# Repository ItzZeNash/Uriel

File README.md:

Fully assembled in fusion 
For assembly solder on the kalih hotswap sockets, the jst connector which is through hold along with the nice!nano clone which is mounted on the backside of the board flipped. The diodes should also be soldered on the backside with the black line on the side of the sqaure hole.Also connect the battery with the jst connector.  After that put on the orings on the protrusions on the pcb then put it into the case(the case should already have 5 layers put together(the solid base the hollow rings x 3, and the gasket holder, after that lay it onto the gasket holder which will support the pcb, then add the other gasket holder to make sure it holds, then add the top 2 whihc inlude a cutout for the usb, then add screws to fasten the case. After that add the m2 standoffs on the pcb where the controller and the silkscreen is then add it onto the holds then screw onto the small acrylic cover and you are finished.

Idk how to do keycaps and nice nano itll be also itll be wayy to complicated for me ._.

# Uriel
A 40% keyboard 
PCB - 

Schem-

Bom

# Bill of Materials (BOM) — Custom 40% Keybiard

| # | Component | Qty | Description / Specs | Part / Model | Price (USD) | Source / Link | Notes |
|---|-----------|-----|---------------------|--------------|-------------|----------------|-------|
| 1 | Wireless Controller | 2 | NRF52840 dev board, Nice!Nano v2 compatible, BLE + charging, Pro Micro footprint | Nice!Nano alternative | **$4.34 each ($8.68)** | https://www.ebay.com/itm/405014063318 | Use as nice_nano_v2 in ZMK. Deep sleep ~1mA. |
| 2 | Keyboard Switches | 90 | Akko Rosewood Linear, 5-pin MX, 40gf, factory lubed | Akko Rosewood | **$29.46 total** | https://www.aliexpress.com/item/1005007227966289.html | 47 used, extras for future builds. |
| 3 | Switching Diodes | 50 | 1N4148 | 1N4148 pack | **$3.00** | https://www.mouser.com/ProductDetail/onsemi/1N4148TR?qs=i4Fj9T%2FoRm%252BOzV8sfXrhvQ%3D%3D | 1 per key + spares. |
| 4 | Reset Tactile Switch | 2 | Right-angle, grounding, 6mm tact, SPST-NO | MJTP1117 | **$0.61 each ($1.22)** | https://www.mouser.com/ProductDetail/642-MJTP1117 | SW2 in schematic. |
| 5 | Controller Socket Pins | ~48 pins | Mill-Max low-profile sockets | 315-43-112-41-003000 | **$5.00** | https://www.mill-max.com | For Pro Micro/Nice!Nano footprint. |
| 6 | Extra IC Socket Pins | 30+ | Mill-Max standard pins | 03320-000-15-000-003-0 | **$2.28** | https://www.mouser.com | For I2C header J1 (OLED/rotary). |
| 7 | LiPo Battery | 1 | 3.7V 2000mAh with JST | EHB 105454A | **$11.99** | — | One battery for wireless half. |
| 8 | Case / Dampening Foam | 1–2 sheets | 3mm PORON/IXPE foam | MEARCOOH 3mm | **$9.96** | — | Sound dampening inside case. |
| 9 | Misc Hardware | Various | Standoffs, screws, bumpers, O-rings | Assorted | **$40.00** | — | Includes PCB standoffs, bumpers, etc. |
| 10 | Hotswap Sockets | 50 | Kailh MX hotswap sockets | Kailh CPG151101 | **$15.00** | https://www.amazon.com/dp/B0BVH6M5FP | Optional. |
| 11 | Keycaps | 1 set | Doubleshot PBT keycaps | Generic | **$13.00** | https://www.amazon.com/gp/product/B0D1JWX3PP | — |

---

## 💵 Total Estimated Cost

**~$253.69 USD** Somewhere there 
Decreased the price with this

Breakdown:
- Controllers: $8.68  
- Switches: $29.46  
- Diodes: $3  
- Reset switches: $1.22  
- Mill‑Max low‑profile: $5  
- Mill‑Max standard: $2.28  
- Battery: $11.99  
- Foam: $9.96  
- Misc hardware: $40  
- Hotswap sockets: $15  
- Keycaps: $13  

**Grand Total: $140.59**

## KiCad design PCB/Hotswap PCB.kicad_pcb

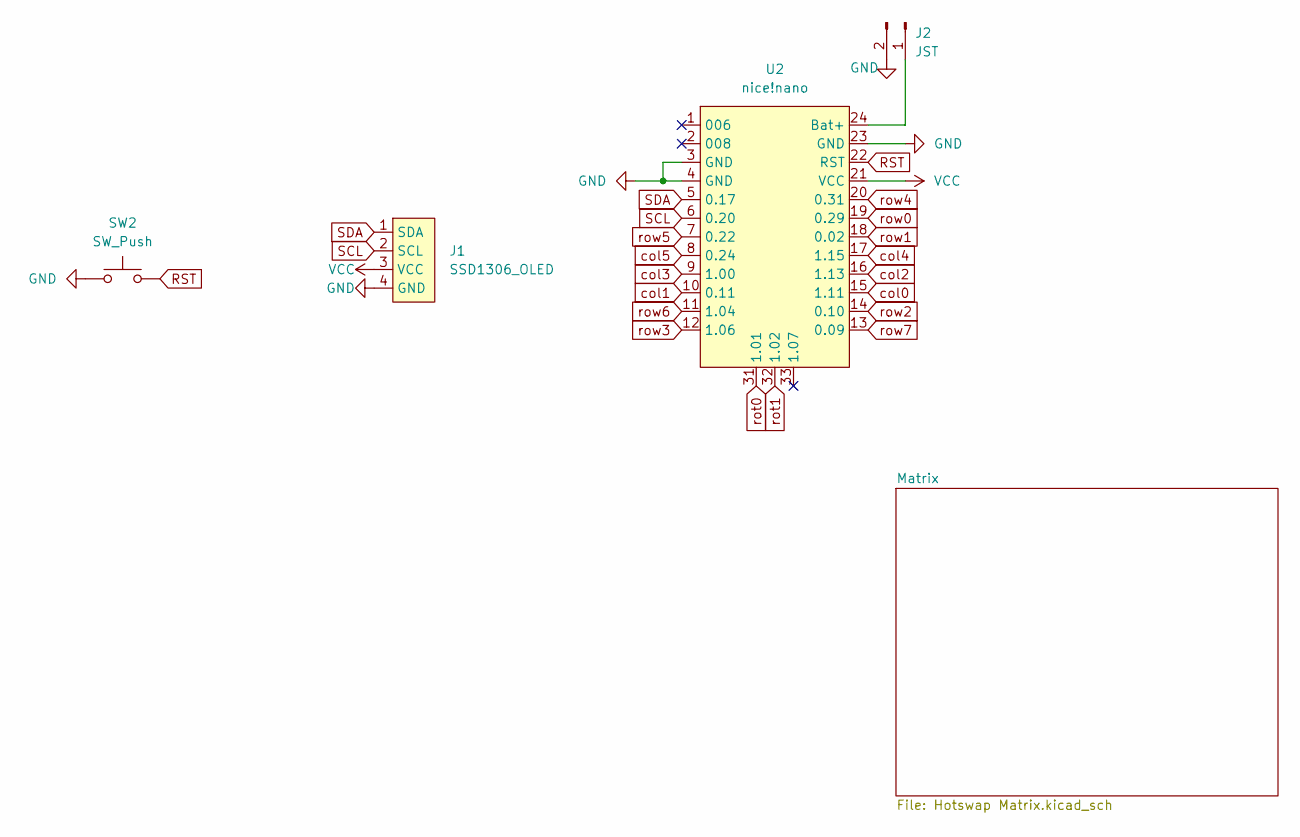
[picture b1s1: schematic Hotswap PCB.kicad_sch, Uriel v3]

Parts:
J1: SSD1306_OLED; OLED_v2
J2: JST; JST_PH_S2B-PH-K_1x02_P2.00mm_Horizontal
SW2: SW_Push; SW_Tactile_SPST_Angled_MJTP1117
U2: nice!nano; nice_nano

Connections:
GND: J1.4 (GND), J2.2, SW2.1, U2.3 (GND), U2.4 (GND), U2.23 (GND); also elsewhere on the board
unnamed: J2.1, U2.24 (Bat+)
RST: SW2.2, U2.22 (RST)
SCL: J1.2 (SCL), U2.6 (0.20)
SDA: J1.1 (SDA), U2.5 (0.17)
VCC: J1.3 (VCC), U2.21 (VCC)
col0: U2.15 (1.11); also elsewhere on the board
col1: U2.10 (0.11); also elsewhere on the board
col2: U2.16 (1.13); also elsewhere on the board
col3: U2.9 (1.00); also elsewhere on the board
col4: U2.17 (1.15); also elsewhere on the board
col5: U2.8 (0.24); also elsewhere on the board
rot0: U2.31 (1.01); also elsewhere on the board
rot1: U2.32 (1.02); also elsewhere on the board
row0: U2.19 (0.29); also elsewhere on the board
row1: U2.18 (0.02); also elsewhere on the board
row2: U2.14 (0.10); also elsewhere on the board
row3: U2.12 (1.06); also elsewhere on the board
row4: U2.20 (0.31); also elsewhere on the board
row5: U2.7 (0.22); also elsewhere on the board
row6: U2.11 (1.04); also elsewhere on the board
row7: U2.13 (0.09); also elsewhere on the board

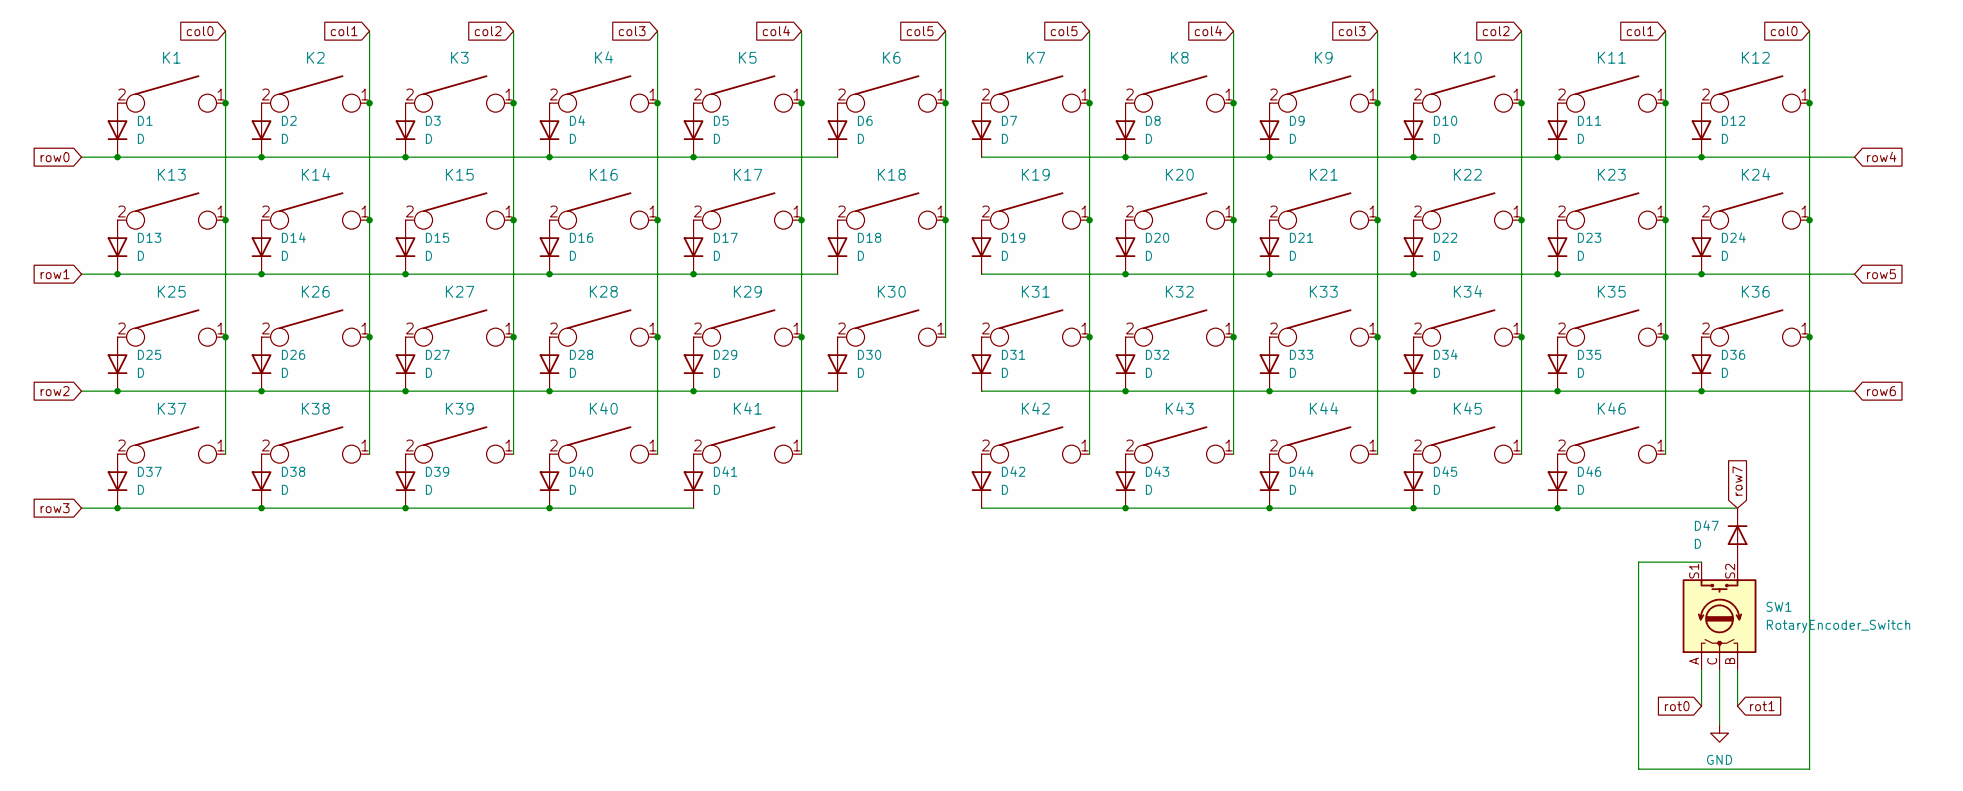
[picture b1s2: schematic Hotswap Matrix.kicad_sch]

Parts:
D1, D2, D3, D4, D5, D6, D7, D8, D9, D10, D11, D12, D13, D14, D15, D16, D17, D18, D19, D20, D21, D22, D23, D24, D25, D26, D27, D28, D29, D30, D31, D32, D33, D34, D35, D36, D37, D38, D39, D40, D41, D42, D43, D44, D45, D46, D47: D; Diode-Hybrid-Back
K1, K2, K3, K4, K5, K6, K7, K8, K9, K10, K11, K14, K15, K16, K17, K18, K19, K20, K21, K22, K23, K26, K27, K28, K29, K30, K31, K32, K33, K34, K35, K36, K37, K38, K39, K40, K43, K44, K45, K46: KEYSW; MXOnly-1U-NoLED
K12, K25: KEYSW; MXOnly-1.5U-NoLED
K13, K24, K41, K42: KEYSW; MXOnly-1.25U-NoLED
SW1: RotaryEncoder_Switch; RotaryEncoder_Alps_EC11E-Switch_Vertical_H20mm

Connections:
GND: SW1.C; also elsewhere on the board
unnamed: D1.2 (A), K1.2
unnamed: D2.2 (A), K2.2
unnamed: D3.2 (A), K3.2
unnamed: D4.2 (A), K4.2
unnamed: D5.2 (A), K5.2
unnamed: D6.2 (A), K6.2
unnamed: D7.2 (A), K7.2
unnamed: D8.2 (A), K8.2
unnamed: D9.2 (A), K9.2
unnamed: D10.2 (A), K10.2
unnamed: D11.2 (A), K11.2
unnamed: D12.2 (A), K12.2
unnamed: D13.2 (A), K13.2
unnamed: D14.2 (A), K14.2
unnamed: D15.2 (A), K15.2
unnamed: D16.2 (A), K16.2
unnamed: D17.2 (A), K17.2
unnamed: D18.2 (A), K18.2
unnamed: D19.2 (A), K19.2
unnamed: D20.2 (A), K20.2
unnamed: D21.2 (A), K21.2
unnamed: D22.2 (A), K22.2
unnamed: D23.2 (A), K23.2
unnamed: D24.2 (A), K24.2
unnamed: D25.2 (A), K25.2
unnamed: D26.2 (A), K26.2
unnamed: D27.2 (A), K27.2
unnamed: D28.2 (A), K28.2
unnamed: D29.2 (A), K29.2
unnamed: D30.2 (A), K30.2
unnamed: D31.2 (A), K31.2
unnamed: D32.2 (A), K32.2
unnamed: D33.2 (A), K33.2
unnamed: D34.2 (A), K34.2
unnamed: D35.2 (A), K35.2
unnamed: D36.2 (A), K36.2
unnamed: D37.2 (A), K37.2
unnamed: D38.2 (A), K38.2
unnamed: D39.2 (A), K39.2
unnamed: D40.2 (A), K40.2
unnamed: D41.2 (A), K41.2
unnamed: D42.2 (A), K42.2
unnamed: D43.2 (A), K43.2
unnamed: D44.2 (A), K44.2
unnamed: D45.2 (A), K45.2
unnamed: D46.2 (A), K46.2
unnamed: D47.2 (A), SW1.S2
col0: K1.1, K12.1, K13.1, K24.1, K25.1, K36.1, K37.1, SW1.S1; also elsewhere on the board
col1: K2.1, K11.1, K14.1, K23.1, K26.1, K35.1, K38.1, K46.1; also elsewhere on the board
col2: K3.1, K10.1, K15.1, K22.1, K27.1, K34.1, K39.1, K45.1; also elsewhere on the board
col3: K4.1, K9.1, K16.1, K21.1, K28.1, K33.1, K40.1, K44.1; also elsewhere on the board
col4: K5.1, K8.1, K17.1, K20.1, K29.1, K32.1, K41.1, K43.1; also elsewhere on the board
col5: K6.1, K7.1, K18.1, K19.1, K30.1, K31.1, K42.1; also elsewhere on the board
rot0: SW1.A; also elsewhere on the board
rot1: SW1.B; also elsewhere on the board
row0: D1.1 (K), D2.1 (K), D3.1 (K), D4.1 (K), D5.1 (K), D6.1 (K); also elsewhere on the board
row1: D13.1 (K), D14.1 (K), D15.1 (K), D16.1 (K), D17.1 (K), D18.1 (K); also elsewhere on the board
row2: D25.1 (K), D26.1 (K), D27.1 (K), D28.1 (K), D29.1 (K), D30.1 (K); also elsewhere on the board
row3: D37.1 (K), D38.1 (K), D39.1 (K), D40.1 (K), D41.1 (K); also elsewhere on the board
row4: D7.1 (K), D8.1 (K), D9.1 (K), D10.1 (K), D11.1 (K), D12.1 (K); also elsewhere on the board
row5: D19.1 (K), D20.1 (K), D21.1 (K), D22.1 (K), D23.1 (K), D24.1 (K); also elsewhere on the board
row6: D31.1 (K), D32.1 (K), D33.1 (K), D34.1 (K), D35.1 (K), D36.1 (K); also elsewhere on the board
row7: D42.1 (K), D43.1 (K), D44.1 (K), D45.1 (K), D46.1 (K), D47.1 (K); also elsewhere on the board

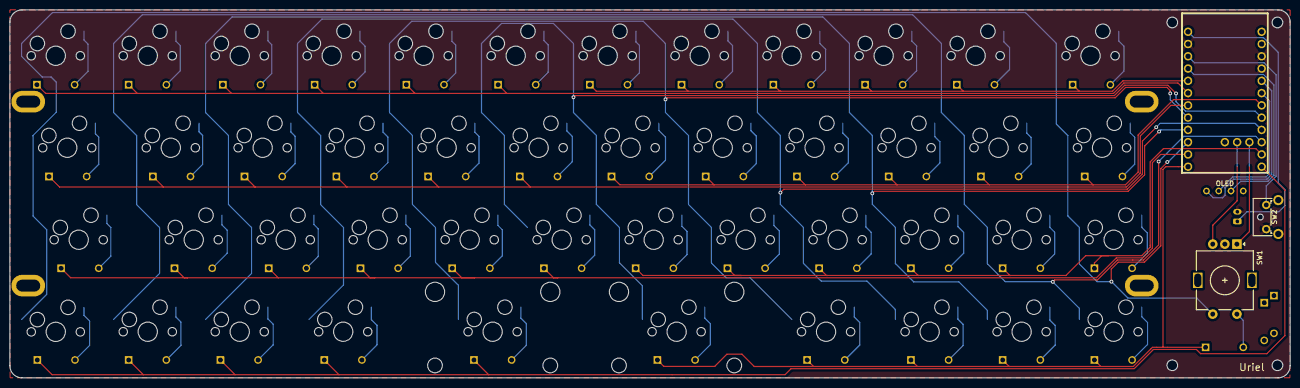
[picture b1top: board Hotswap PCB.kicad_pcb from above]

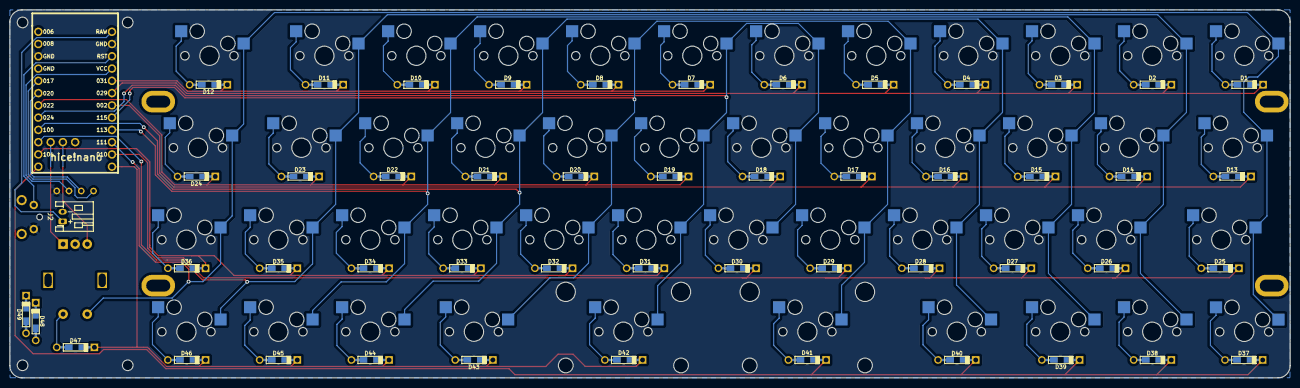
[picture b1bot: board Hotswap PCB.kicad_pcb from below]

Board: 2 copper layers, 265.1 x 76.2 mm, 108 parts (2 on the bottom side), 69 nets.

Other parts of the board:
Acryl Mount: MountingHole_2.2mm_M2
Acryl Mount#2, Acryl Mount#3, Acryl Mount#4: MountingHole_2.2mm_M2
D48, D49: D; Diode-Hybrid-Back
Mnt: PKRH
Mnt#2, Mnt#3, Mnt#4: PKRH

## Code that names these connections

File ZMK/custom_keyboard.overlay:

/ {
    chosen {
        zmk,kscan = &kscan0;
        zmk,matrix_transform = &default_transform;
    };

    default_transform: keymap_transform_0 {
        compatible = "zmk,matrix-transform";
        columns = <10>;
        rows = <4>;
        
        map = <
            RC(0,0) RC(0,1) RC(0,2) RC(0,3) RC(0,4) RC(0,5) RC(0,6) RC(0,7) RC(0,8) RC(0,9)
            RC(1,0) RC(1,1) RC(1,2) RC(1,3) RC(1,4) RC(1,5) RC(1,6) RC(1,7) RC(1,8) RC(1,9)
            RC(2,0) RC(2,1) RC(2,2) RC(2,3) RC(2,4) RC(2,5) RC(2,6) RC(2,7) RC(2,8) RC(2,9)
            RC(3,0) RC(3,1) RC(3,2)         RC(3,3)         RC(3,4) RC(3,5) RC(3,6) RC(3,7)
        >;
    };

    kscan0: kscan {
        compatible = "zmk,kscan-gpio-matrix";
        label = "KSCAN";
        
        diode-direction = "col2row";
        
        row-gpios
            = <&gpio0 17 (GPIO_ACTIVE_HIGH | GPIO_PULL_DOWN)>  // ROW0
            , <&gpio0 20 (GPIO_ACTIVE_HIGH | GPIO_PULL_DOWN)>  // ROW1
            , <&gpio0 22 (GPIO_ACTIVE_HIGH | GPIO_PULL_DOWN)>  // ROW2
            , <&gpio0 24 (GPIO_ACTIVE_HIGH | GPIO_PULL_DOWN)>  // ROW3
            ;
        
        col-gpios
            = <&gpio1  0 GPIO_ACTIVE_HIGH>  // COL0
            , <&gpio1  4 GPIO_ACTIVE_HIGH>  // COL1
            , <&gpio1  6 GPIO_ACTIVE_HIGH>  // COL2
            , <&gpio0 11 GPIO_ACTIVE_HIGH>  // COL3
            , <&gpio1 11 GPIO_ACTIVE_HIGH>  // COL4
            , <&gpio1 13 GPIO_ACTIVE_HIGH>  // COL5
            , <&gpio1 15 GPIO_ACTIVE_HIGH>  // COL6
            , <&gpio0 2  GPIO_ACTIVE_HIGH>  // COL7
            , <&gpio0 29 GPIO_ACTIVE_HIGH>  // COL8
            , <&gpio0 31 GPIO_ACTIVE_HIGH>  // COL9
            ;
    };
};

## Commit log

2025-12-31 Add new temporary file in Gerbers directory
2025-12-31 Add new temporary file in PCB directory
2025-12-31 Create temp
2025-12-31 Enhance README with PCB and schematic images
    Added images for PCB and schematic to README.
2026-01-01 Add new temporary file in CAD directory
2026-01-01 Add temp file to Firmware ZMK directory
2026-01-01 Remove license comment from urielv1.keymap
    Removed license comment block from keymap file.
2026-01-22 Update hotswap sockets quantity and link
    Updated the quantity of hotswap sockets and modified the AliExpress link for better clarity.
2026-01-22 Revise BOM for Custom 47-Key Split Ergo Keyboard
    Updated the Bill of Materials (BOM) for the custom keyboard, including component details, quantities, prices, and sources.
2026-01-22 Update BOM title and correct keyboard type
2026-01-22 Add files via upload
    Acrylic case files
2026-01-23 Add files via upload
    Upladed the step of the pcb and plate
2026-01-23 Add files via upload
    Plate gerbers
2026-01-23 Add new temporary file in ZMK directory
2026-01-23 Add custom keyboard configuration to Kconfig
2026-01-23 Add custom keyboard overlay configuration
2026-01-23 Add custom_keyboard.keymap with default layer
    Define a custom keymap for the keyboard with default layer bindings.
2026-01-23 Enhance README with assembly instructions
    Added detailed assembly instructions for the keyboard.
2026-01-23 Revise total estimated cost and add price decrease note
    Updated total estimated cost and added a price decrease note with an image.
2026-01-23 Add files via upload
    plate
